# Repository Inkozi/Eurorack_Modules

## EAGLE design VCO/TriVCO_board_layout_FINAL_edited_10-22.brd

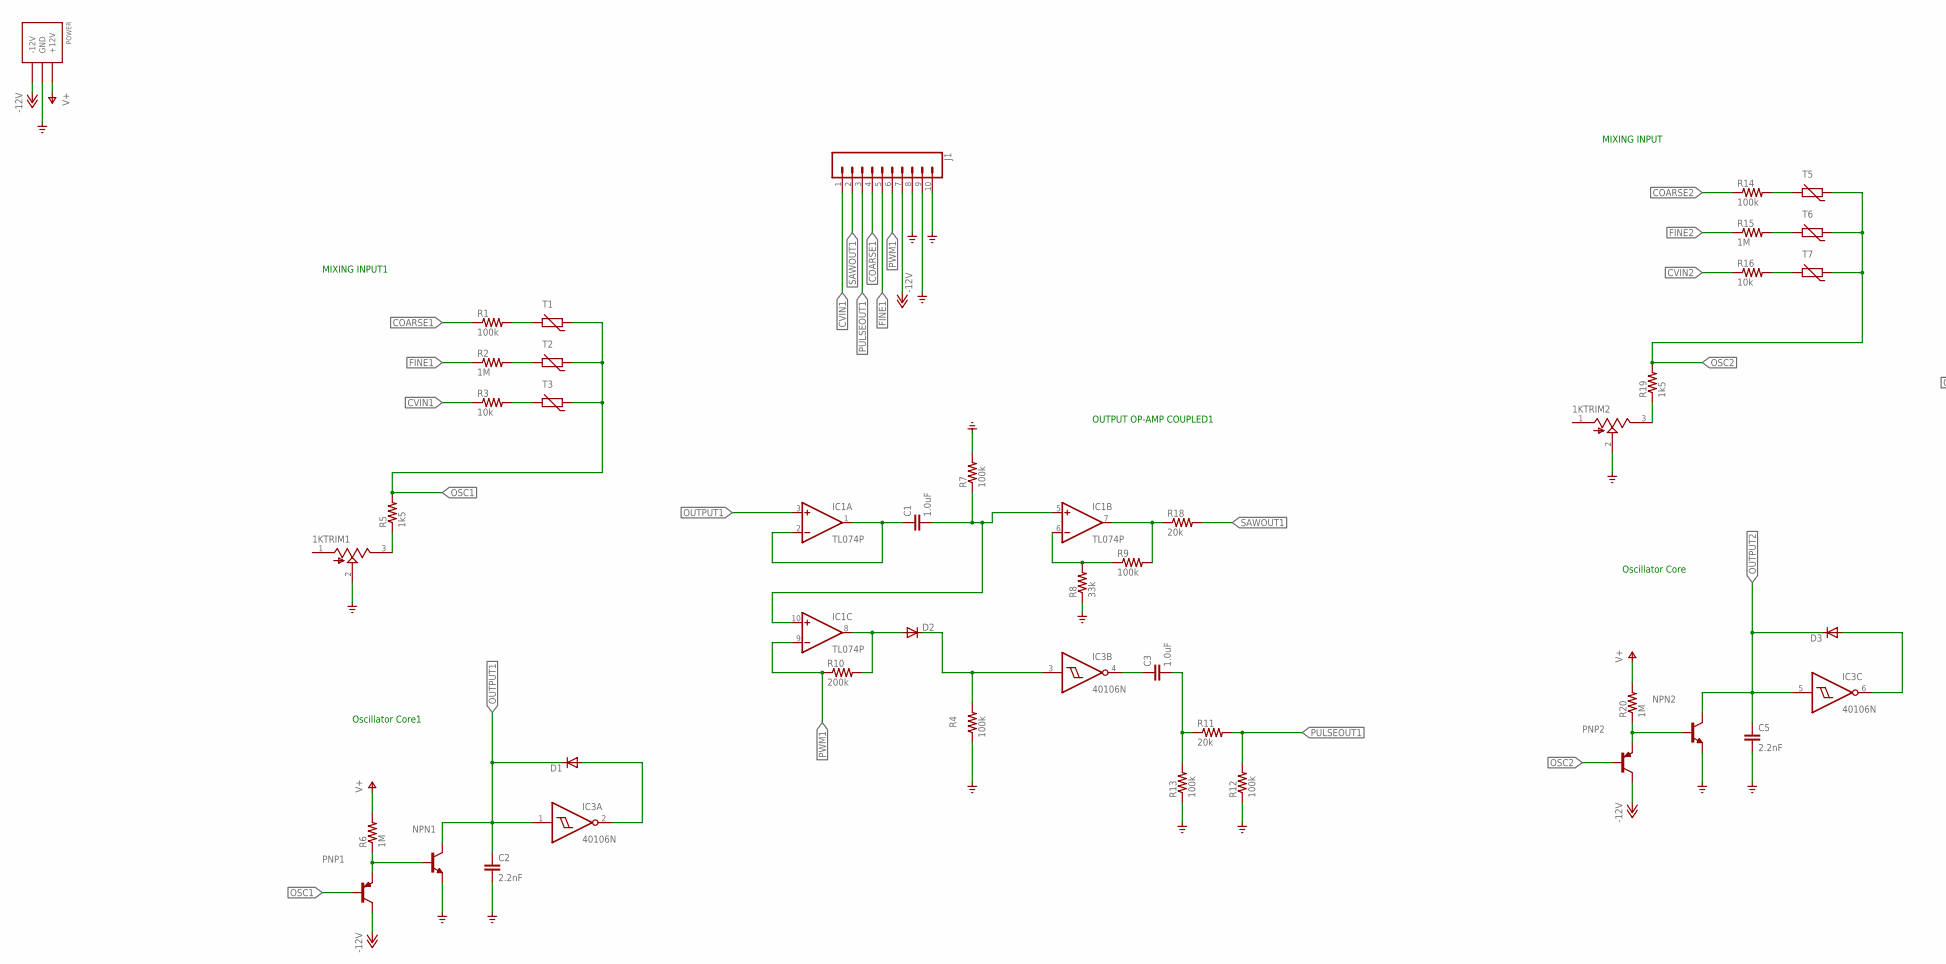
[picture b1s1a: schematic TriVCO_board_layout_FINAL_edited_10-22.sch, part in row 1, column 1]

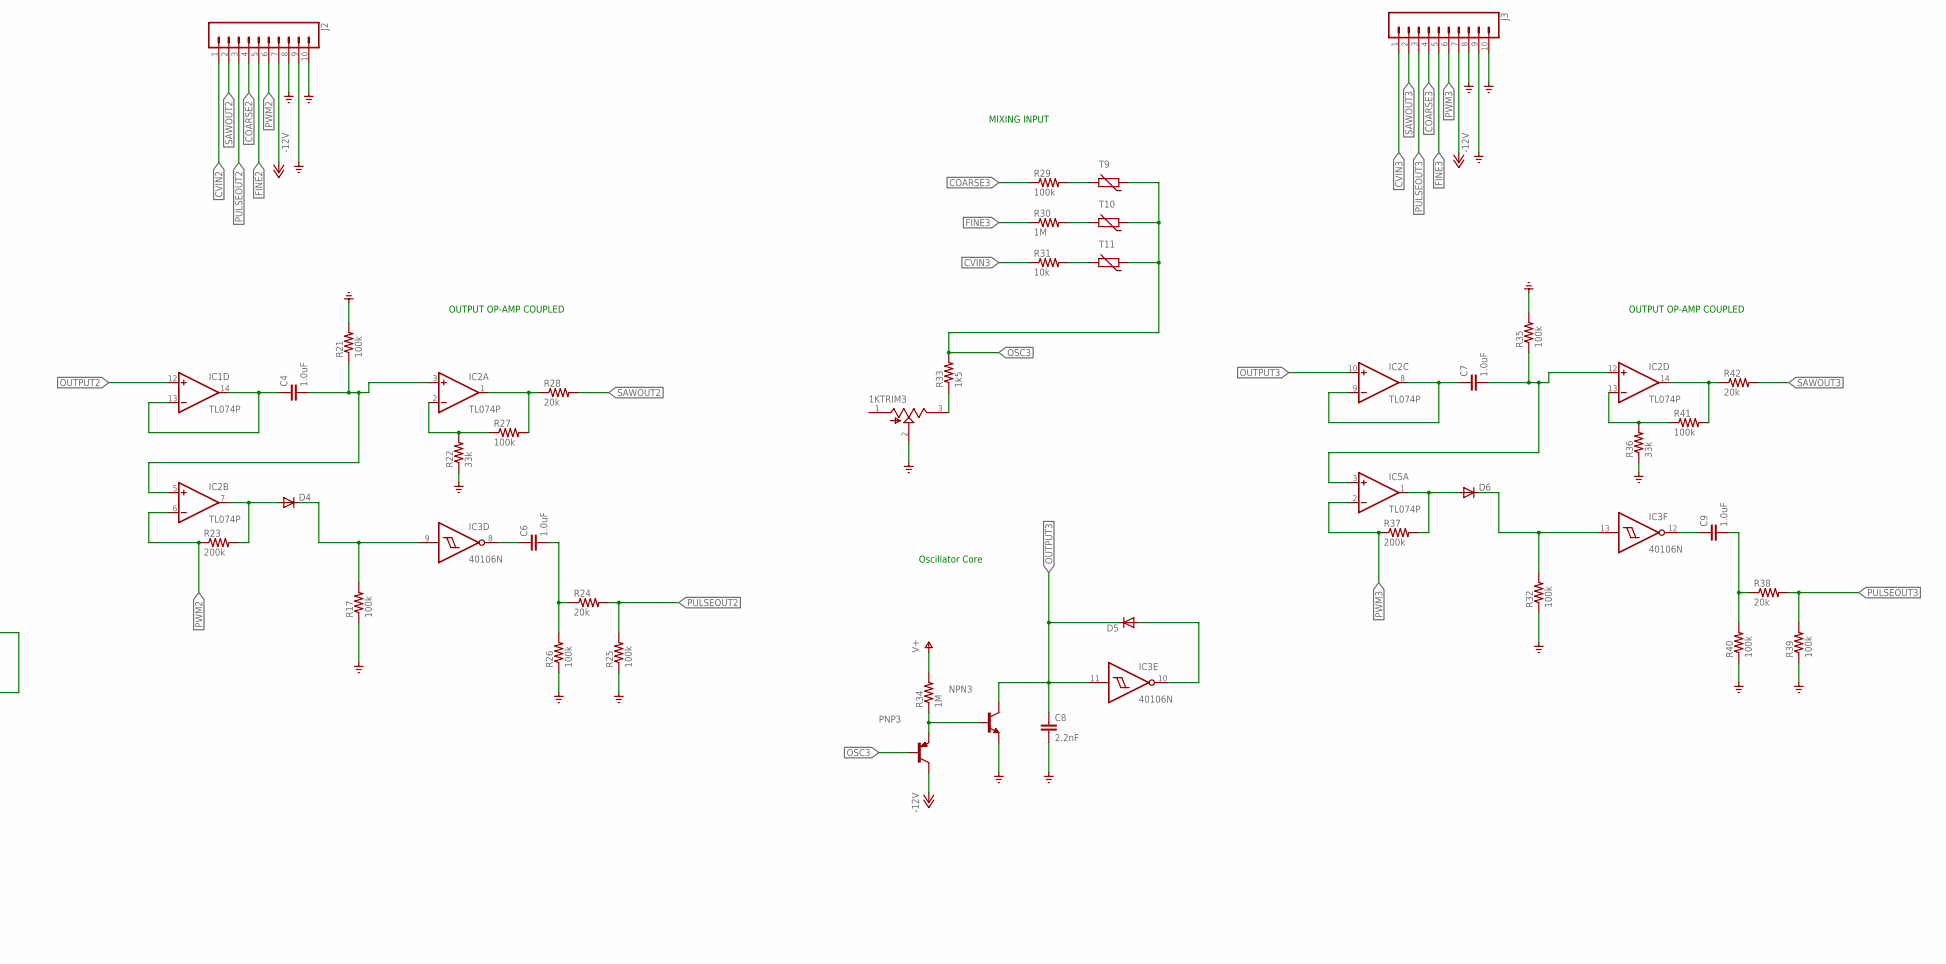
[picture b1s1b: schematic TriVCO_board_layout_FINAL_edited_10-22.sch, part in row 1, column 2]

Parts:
1KTRIM1, 1KTRIM2, 1KTRIM3: 3362P-1-102LF; TRIM_3362P-1-102LF
C1, C4, C7: 1.0uF; 0603
C2, C5, C8: 2.2nF; 0603
C3, C6, C9: 1.0uF; 0402
D1, D2, D3, D4, D5, D6: 1N4148DO35-7; DO35-7
IC1, IC2, IC5: TL074P; DIL14
IC3: 40106N; DIL14
J1, J2, J3: CONN_10"; 1X10
NPN1, NPN2, NPN3: BC485-NPN-TO92-CBE; TO92-CBE
PNP1, PNP2, PNP3: BC450-PNP-TO92-EBC; TO92-EBC
POWER: POWER_SIMPLE10; POWER_10
R1, R4, R7, R9, R12, R13, R14, R17, R21, R25, R26, R27, R29, R32, R35, R39, R40, R41: 100k; 0207/10
R2, R6, R15, R20, R30, R34: 1M; 0207/10
R3, R16, R31: 10k; 0207/10
R5, R19, R33: 1k5; 0207/10
R8, R22, R36: 33k; 0207/10
R10, R23, R37: 200k; 0207/10
R11, R18, R24, R28, R38, R42: 20k; 0207/10
T1, T2, T3, T5, T6, T7, T9, T10, T11: THERMISTOR-5; R-5

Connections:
COARSE1: J1.4, R1.1
COARSE2: J2.4, R14.1
COARSE3: J3.4, R29.1
CVIN1: J1.1, R3.1
CVIN2: J2.1, R16.1
CVIN3: J3.1, R31.1
FINE1: J1.5, R2.1
FINE2: J2.5, R15.1
FINE3: J3.5, R30.1
GND: 1KTRIM1.2 (WIPER), 1KTRIM2.2 (WIPER), 1KTRIM3.2 (WIPER), C2.2, C5.2, C8.2, IC3.7 (VSS), J1.8, J1.9, J1.10, J2.8, J2.9, J2.10, J3.8, J3.9, J3.10, NPN1.E, NPN2.E, NPN3.E, POWER.3 (GND), POWER.4 (GND), POWER.5 (GND), POWER.6 (GND), POWER.7 (GND), POWER.8 (GND), R4.1, R7.2, R8.1, R12.1, R13.1, R17.1, R21.2, R22.1, R25.1, R26.1, R32.1, R35.2, R36.1, R39.1, R40.1
unnamed: R14.2, T5.2
unnamed: R1.2, T1.2
unnamed: R15.2, T6.2
unnamed: R2.2, T2.2
unnamed: R16.2, T7.2
unnamed: 1KTRIM2.3 (CW), R19.1
unnamed: R3.2, T3.2
unnamed: 1KTRIM1.3 (CW), R5.1
unnamed: NPN1.B, PNP1.E, R6.1
unnamed: NPN2.B, PNP2.E, R20.1
unnamed: D1.A, IC3.2 (O)
unnamed: D3.A, IC3.6 (O)
unnamed: C1.1, IC1.1 (OUT), IC1.2 (-IN)
unnamed: C1.2, IC1.5 (+IN), IC1.10 (+IN), R7.1
unnamed: IC1.6 (-IN), R8.2, R9.1
unnamed: IC1.7 (OUT), R9.2, R18.1
unnamed: C4.1, IC1.13 (-IN), IC1.14 (OUT)
unnamed: D2.A, IC1.8 (OUT), R10.2
unnamed: C4.2, IC2.3 (+IN), IC2.5 (+IN), R21.1
unnamed: D2.C, IC3.3 (I), R4.2
unnamed: C3.1, IC3.4 (O)
unnamed: C3.2, R11.1, R13.2
unnamed: IC2.2 (-IN), R22.2, R27.1
unnamed: IC2.1 (OUT), R27.2, R28.1
unnamed: D4.A, IC2.7 (OUT), R23.2
unnamed: D4.C, IC3.9 (I), R17.2
unnamed: C6.1, IC3.8 (O)
unnamed: C6.2, R24.1, R26.2
unnamed: R29.2, T9.2
unnamed: R30.2, T10.2
unnamed: R31.2, T11.2
unnamed: 1KTRIM3.3 (CW), R33.1
unnamed: NPN3.B, PNP3.E, R34.1
unnamed: D5.A, IC3.10 (O)
unnamed: C7.1, IC2.8 (OUT), IC2.9 (-IN)
unnamed: C7.2, IC2.12 (+IN), IC5.3 (+IN), R35.1
unnamed: IC2.13 (-IN), R36.2, R41.1
unnamed: IC2.14 (OUT), R41.2, R42.1
unnamed: D6.A, IC5.1 (OUT), R37.2
unnamed: D6.C, IC3.13 (I), R32.2
unnamed: C9.1, IC3.12 (O)
unnamed: C9.2, R38.1, R40.2
OSC1: PNP1.B, R5.2, T1.1, T2.1, T3.1
OSC2: PNP2.B, R19.2, T5.1, T6.1, T7.1
OSC3: PNP3.B, R33.2, T9.1, T10.1, T11.1
OUTPUT1: C2.1, D1.C, IC1.3 (+IN), IC3.1 (I), NPN1.C
OUTPUT2: C5.1, D3.C, IC1.12 (+IN), IC3.5 (I), NPN2.C
OUTPUT3: C8.1, D5.C, IC2.10 (+IN), IC3.11 (I), NPN3.C
PULSEOUT1: J1.3, R11.2, R12.2
PULSEOUT2: J2.3, R24.2, R25.2
PULSEOUT3: J3.3, R38.2, R39.2
PWM1: IC1.9 (-IN), J1.6, R10.1
PWM2: IC2.6 (-IN), J2.6, R23.1
PWM3: IC5.2 (-IN), J3.6, R37.1
SAWOUT1: J1.2, R18.2
SAWOUT2: J2.2, R28.2
SAWOUT3: J3.2, R42.2
V+: IC1.4 (V+), IC2.4 (V+), IC3.14 (VDD), IC5.4 (V+), POWER.9 (+12V), POWER.10 (+12V), R6.2, R20.2, R34.2
V-: IC1.11 (V-), IC2.11 (V-), IC5.11 (V-), J1.7, J2.7, J3.7, PNP1.C, PNP2.C, PNP3.C, POWER.1 (-12V), POWER.2 (-12V)

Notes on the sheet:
Oscillator Core1
Oscillator Core
OUTPUT OP-AMP COUPLED
OUTPUT OP-AMP COUPLED1
MIXING INPUT
MIXING INPUT1

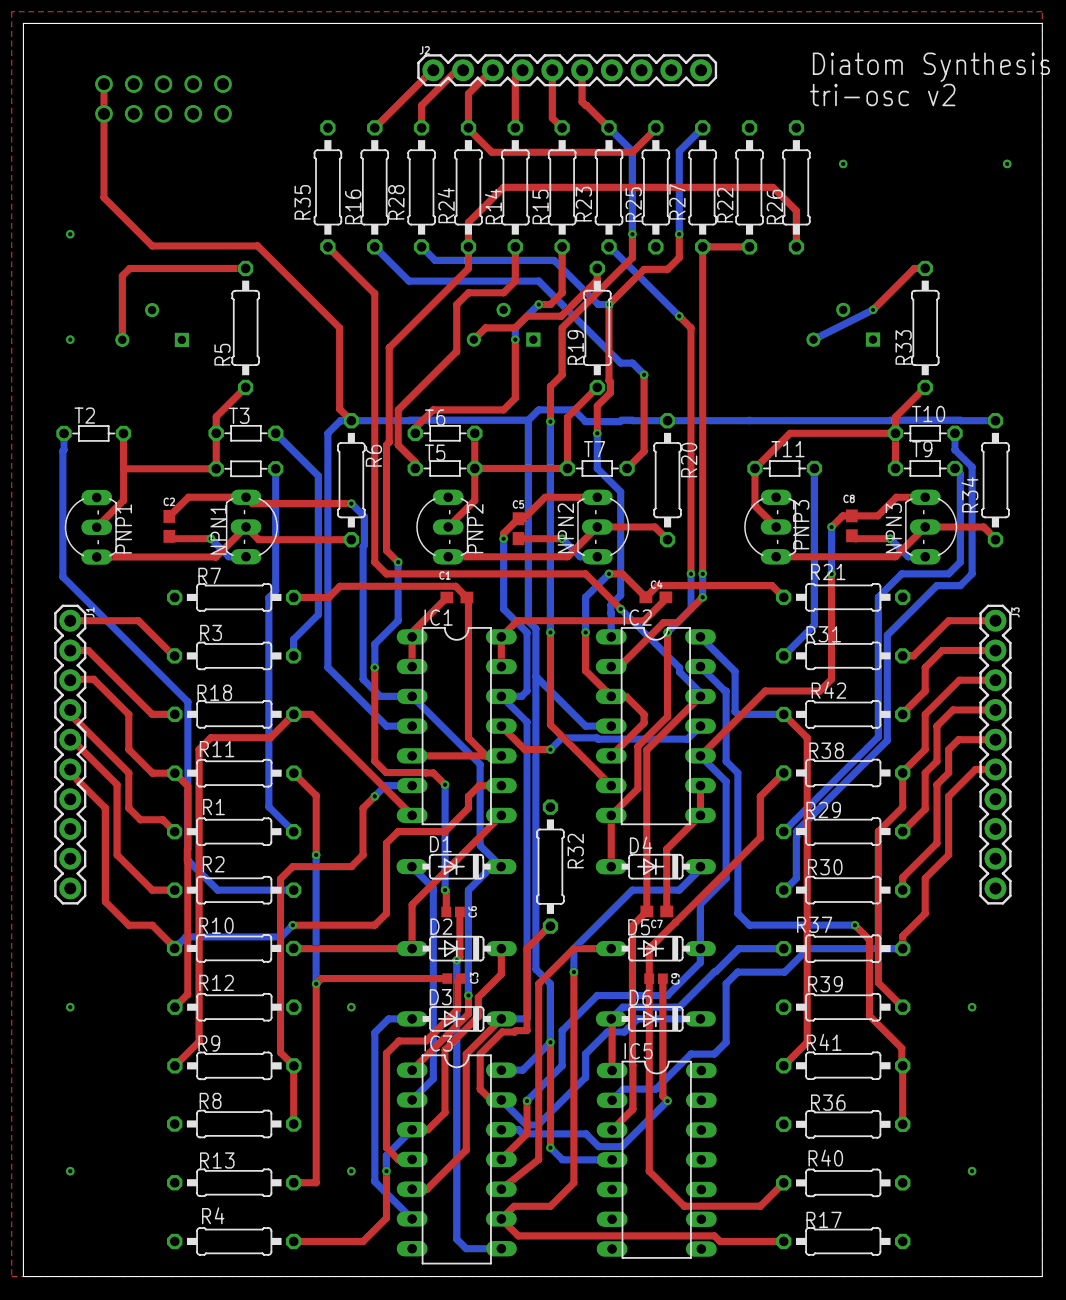
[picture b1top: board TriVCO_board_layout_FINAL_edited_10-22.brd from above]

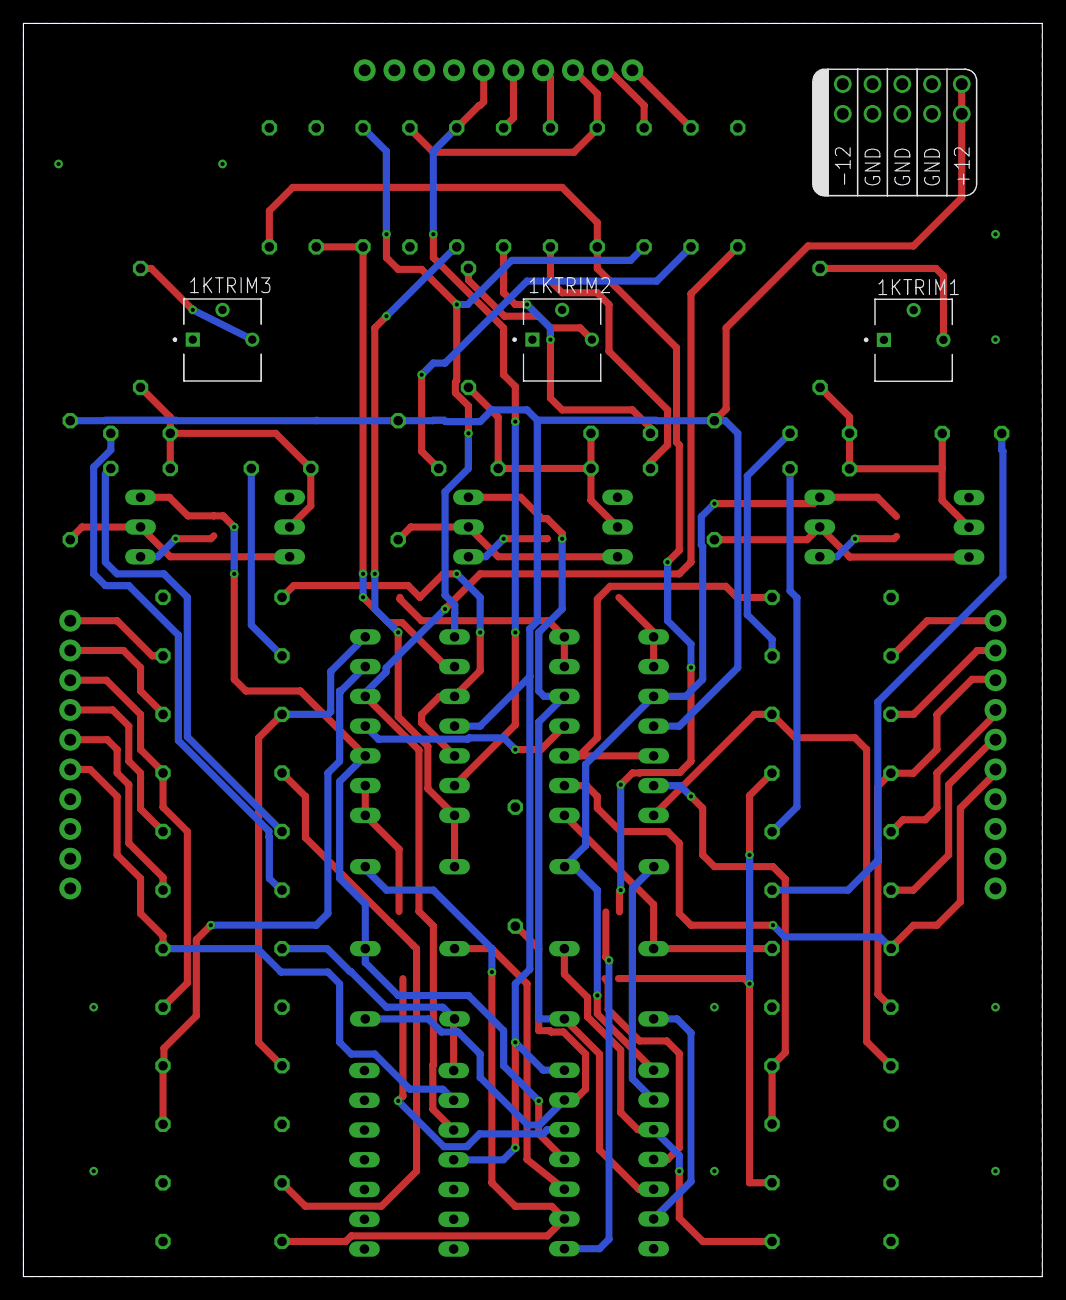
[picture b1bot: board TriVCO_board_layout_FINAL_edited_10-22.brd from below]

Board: 2 copper layers, 87.0 x 107.0 mm, 83 parts (4 on the bottom side), 69 nets.

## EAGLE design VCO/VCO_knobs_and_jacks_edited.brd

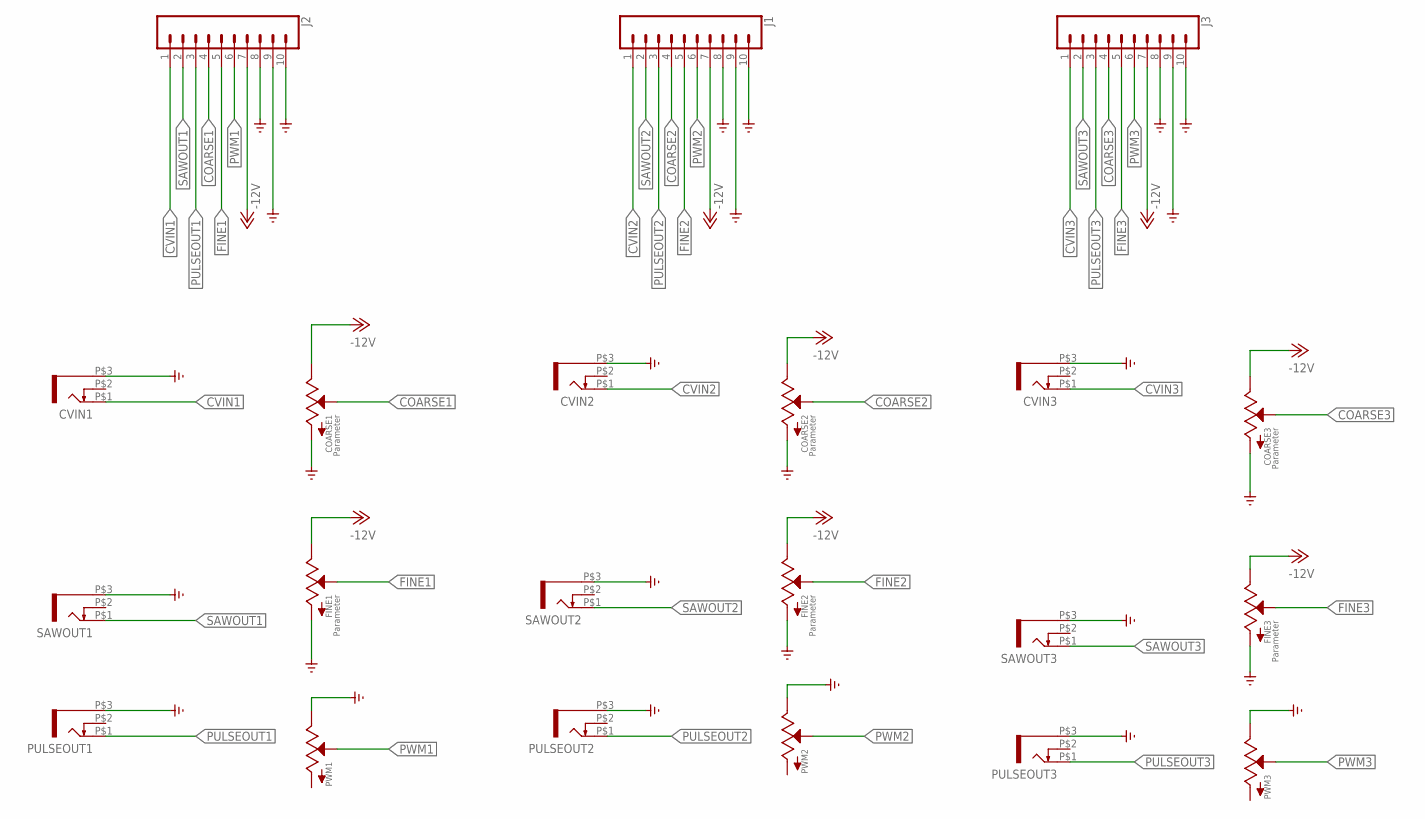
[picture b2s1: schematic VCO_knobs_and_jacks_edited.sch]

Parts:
COARSE1, COARSE2, COARSE3: POTZEPHPOT; OG-POTS_ALPS_POT_VERTICAL
CVIN1, CVIN2, CVIN3: WQP-PJ301M-12_JACK
FINE1, FINE2, FINE3: POTZEPHPOT; OG-POTS_ALPS_POT_VERTICAL
J1, J2, J3: CONN_10"; 1X10
PULSEOUT1, PULSEOUT2, PULSEOUT3: WQP-PJ301M-12_JACK
PWM1, PWM2, PWM3: POTZEPHPOT; OG-POTS_ALPS_POT_VERTICAL
SAWOUT1, SAWOUT2, SAWOUT3: WQP-PJ301M-12_JACK

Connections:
-12V: COARSE1.P$1 (E), COARSE2.P$1 (E), COARSE3.P$1 (E), FINE1.P$1 (E), FINE2.P$1 (E), FINE3.P$1 (E), J1.7, J2.7, J3.7
COARSE1: COARSE1.P$2 (S), J2.4
COARSE2: COARSE2.P$2 (S), J1.4
COARSE3: COARSE3.P$2 (S), J3.4
CVIN1: CVIN1.P$1 (2), J2.1
CVIN2: CVIN2.P$1 (2), J1.1
CVIN3: CVIN3.P$1 (2), J3.1
FINE1: FINE1.P$2 (S), J2.5
FINE2: FINE2.P$2 (S), J1.5
FINE3: FINE3.P$2 (S), J3.5
GND: COARSE1.P$3 (A), COARSE2.P$3 (A), COARSE3.P$3 (A), CVIN1.P$3 (1), CVIN2.P$3 (1), CVIN3.P$3 (1), FINE1.P$3 (A), FINE2.P$3 (A), FINE3.P$3 (A), J1.8, J1.9, J1.10, J2.8, J2.9, J2.10, J3.8, J3.9, J3.10, PULSEOUT1.P$3 (1), PULSEOUT2.P$3 (1), PULSEOUT3.P$3 (1), PWM1.P$1 (E), PWM2.P$1 (E), PWM3.P$1 (E), SAWOUT1.P$3 (1), SAWOUT2.P$3 (1), SAWOUT3.P$3 (1)
PULSEOUT1: J2.3, PULSEOUT1.P$1 (2)
PULSEOUT2: J1.3, PULSEOUT2.P$1 (2)
PULSEOUT3: J3.3, PULSEOUT3.P$1 (2)
PWM1: J2.6, PWM1.P$2 (S)
PWM2: J1.6, PWM2.P$2 (S)
PWM3: J3.6, PWM3.P$2 (S)
SAWOUT1: J2.2, SAWOUT1.P$1 (2)
SAWOUT2: J1.2, SAWOUT2.P$1 (2)
SAWOUT3: J3.2, SAWOUT3.P$1 (2)

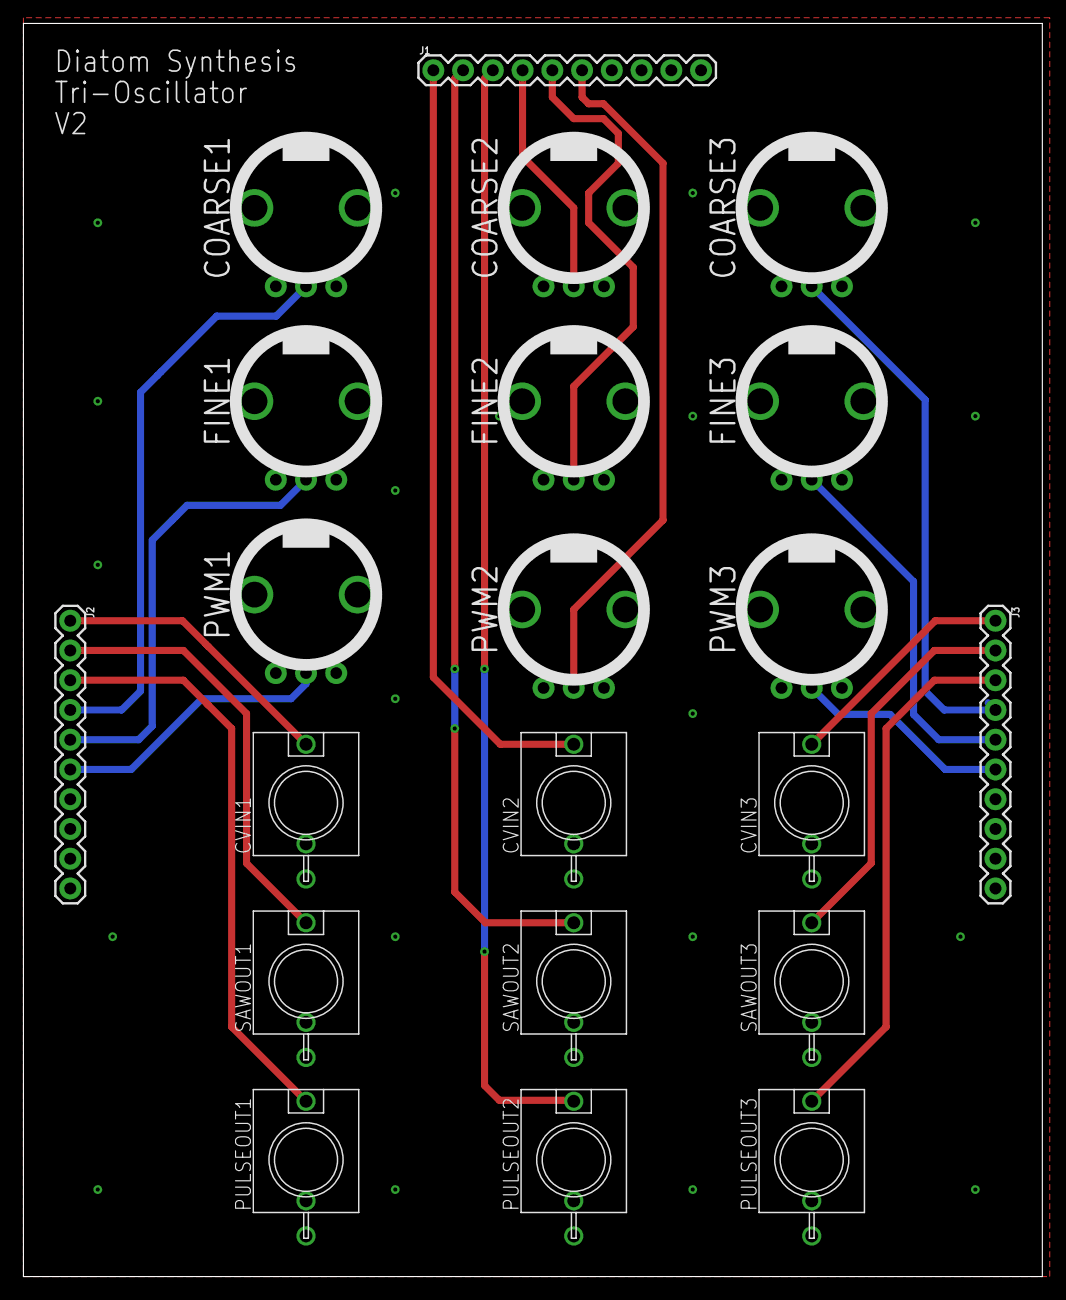
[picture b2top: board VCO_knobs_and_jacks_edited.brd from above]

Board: 2 copper layers, 87.0 x 107.0 mm, 21 parts (0 on the bottom side), 20 nets.

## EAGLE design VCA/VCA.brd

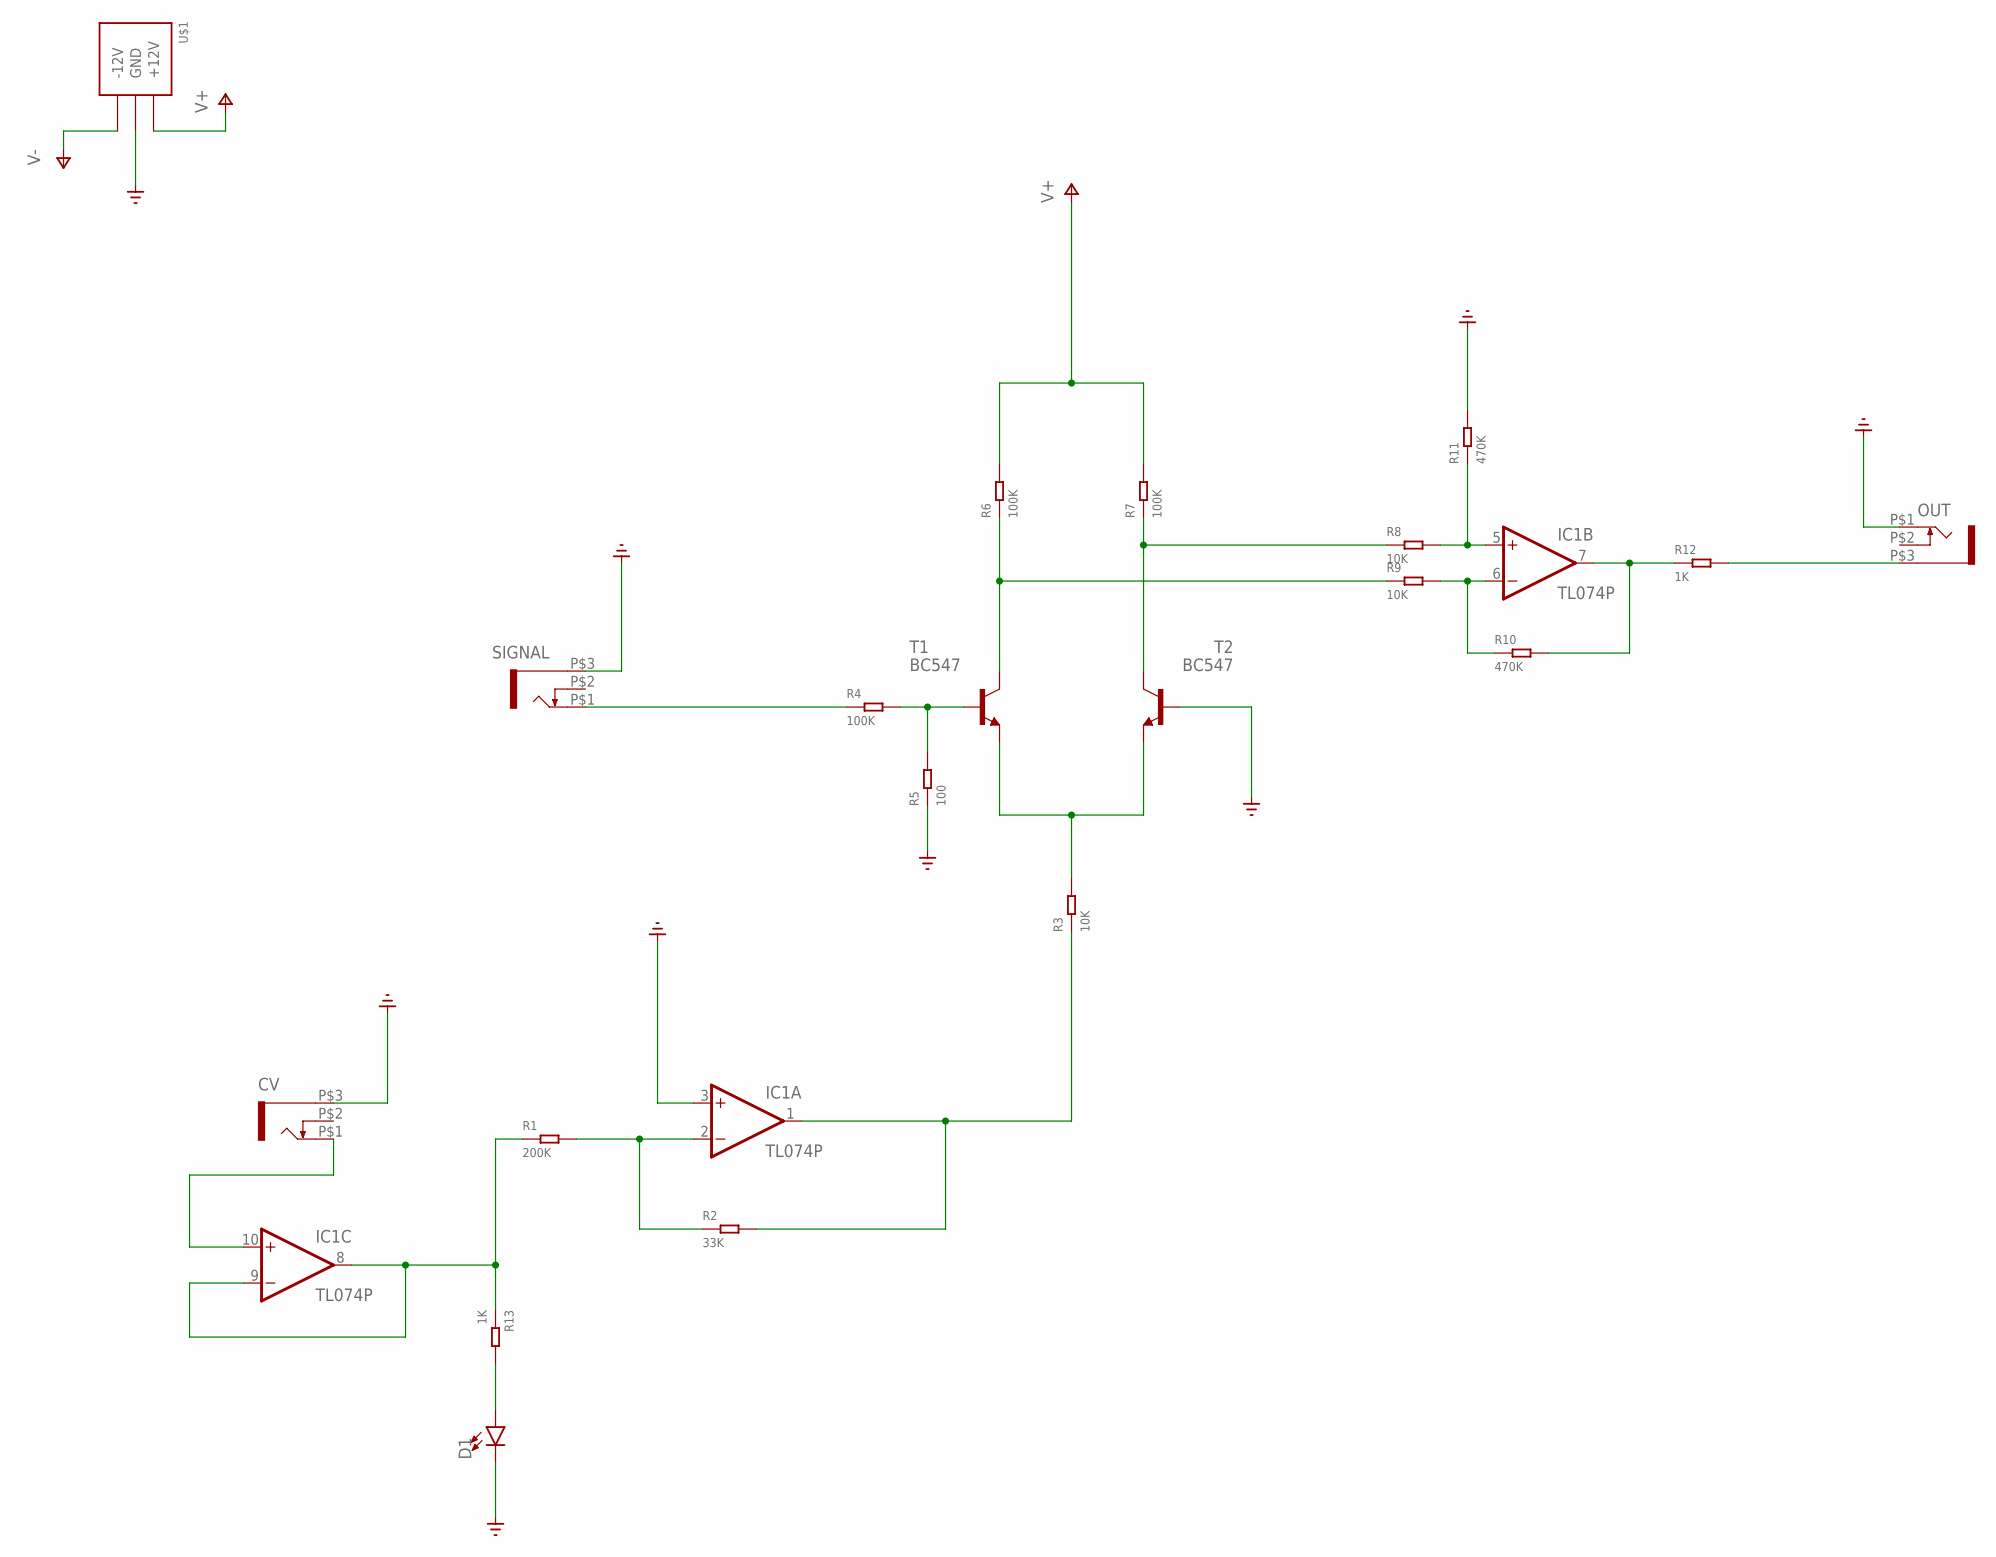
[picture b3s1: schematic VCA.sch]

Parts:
CV: WQP-PJ301M-12_JACK
D1: LED3MM; LED_3MM
IC1: TL074P; DIL14
OUT: WQP-PJ301M-12_JACK
R1: 200K; PR-D2.3XL6.5MM
R2: 33K; PR-D2.3XL6.5MM
R3, R8, R9: 10K; PR-D2.3XL6.5MM
R4, R6, R7: 100K; PR-D2.3XL6.5MM
R5: 100; PR-D2.3XL6.5MM
R10, R11: 470K; PR-D2.3XL6.5MM
R12, R13: 1K; PR-D2.3XL6.5MM
SIGNAL: WQP-PJ301M-12_JACK
T1, T2: BC547; TO92
U$1: POWER_SIMPLE10; POWER_10

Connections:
GND: CV.P$3 (1), D1.K (C), IC1.3 (+IN), OUT.P$1 (2), R5.1, R11.2, SIGNAL.P$3 (1), T2.2 (B), U$1.3 (GND), U$1.4 (GND), U$1.5 (GND), U$1.6 (GND), U$1.7 (GND), U$1.8 (GND)
unnamed: IC1.2 (-IN), R1.2, R2.1
unnamed: R3.2, T1.1 (E), T2.1 (E)
unnamed: IC1.1 (OUT), R2.2, R3.1
unnamed: R4.1, SIGNAL.P$1 (2)
unnamed: R4.2, R5.2, T1.2 (B)
unnamed: CV.P$1 (2), IC1.10 (+IN)
unnamed: R6.1, R9.1, T1.3 (C)
unnamed: R7.1, R8.1, T2.3 (C)
unnamed: IC1.8 (OUT), IC1.9 (-IN), R1.1, R13.1
unnamed: IC1.5 (+IN), R8.2, R11.1
unnamed: IC1.6 (-IN), R9.2, R10.1
unnamed: IC1.7 (OUT), R10.2, R12.1
unnamed: OUT.P$3 (1), R12.2
unnamed: D1.A, R13.2
V+: IC1.4 (V+), R6.2, R7.2, U$1.9 (+12V), U$1.10 (+12V)
V-: IC1.11 (V-), U$1.1 (-12V), U$1.2 (-12V)

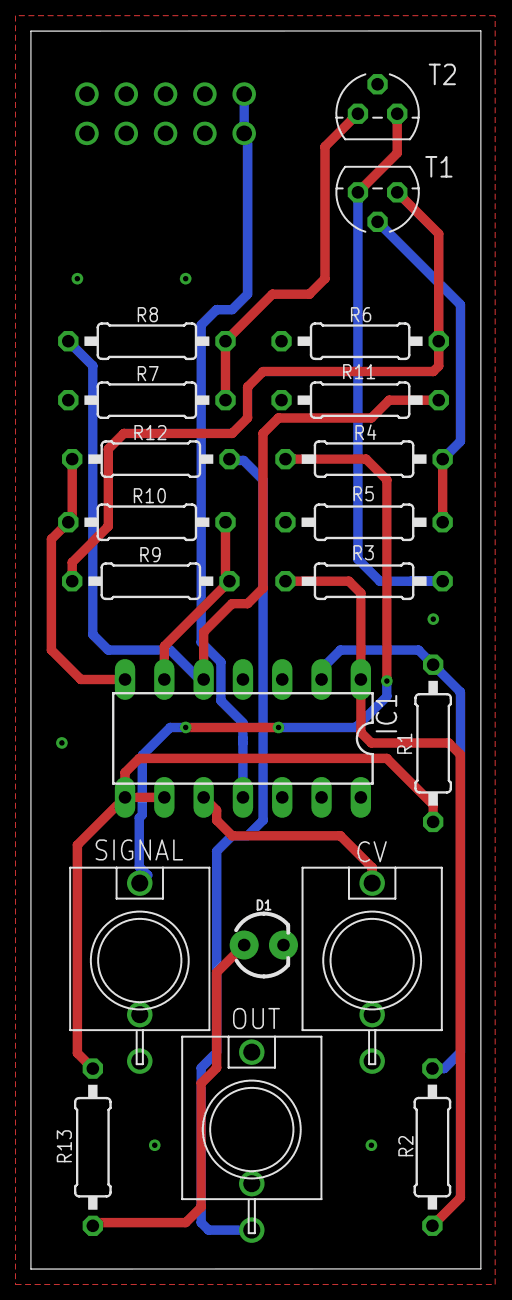
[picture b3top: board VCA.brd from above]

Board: 2 copper layers, 29.1 x 80.0 mm, 21 parts (1 on the bottom side), 17 nets.

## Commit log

2021-10-29 Add files via upload
    Added Finalized VCA schematic and pcb.
2021-10-29 Add files via upload
    VCO, still a work in progress but getting close.
2021-10-29 Add files via upload
    Bill of Materials and Parts List

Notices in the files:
parts and their libraries:
SparkFun-LED: Licensing: Creative Commons ShareAlike 4.0 International - https://creativecommons.org/licenses/by-sa/4.0
